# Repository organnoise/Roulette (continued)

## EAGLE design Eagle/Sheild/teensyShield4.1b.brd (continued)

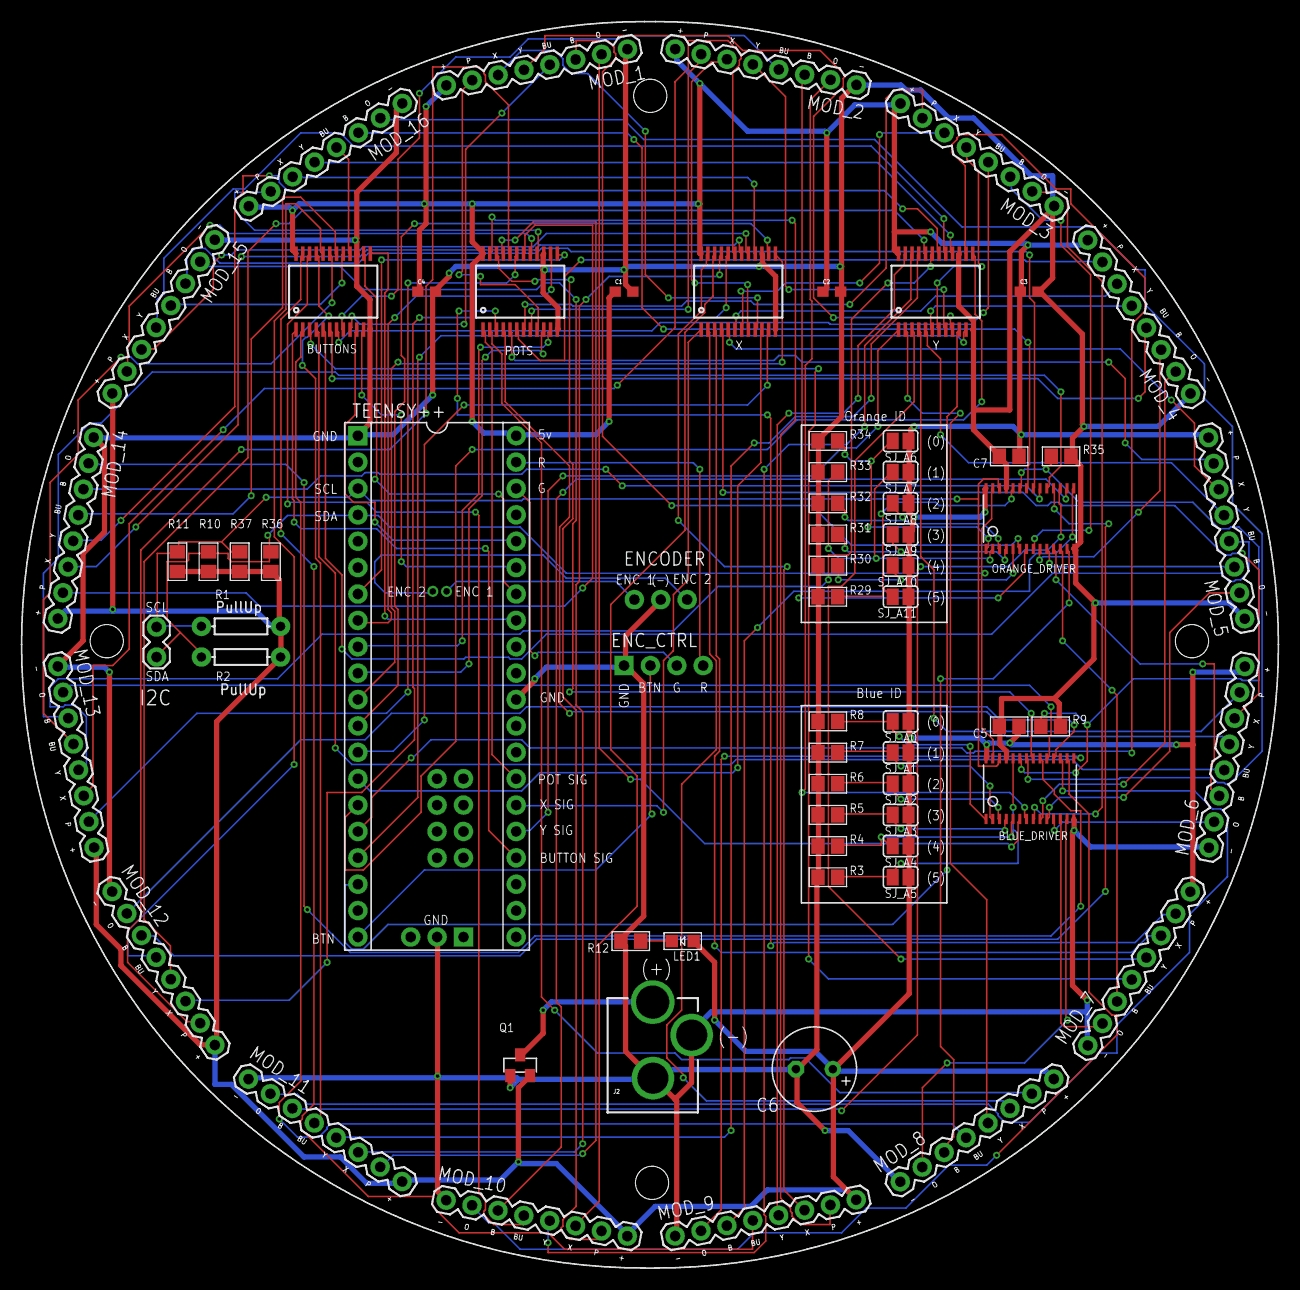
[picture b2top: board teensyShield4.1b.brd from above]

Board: 2 copper layers, 121.0 x 120.0 mm, 69 parts (0 on the bottom side), 140 nets.
